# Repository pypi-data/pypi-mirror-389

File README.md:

# PyPI code 389

This repository is part of a project to make all code in PyPI as accessible as possible. For more information 
on the project and to find out how to utilise this data, see the website: https://py-code.org/

This repo contains 50000 packages uploaded to PyPI between 
2025-11-03 04:11 and 2025-11-06 15:08.

The repo is 99% (49999/50000) complete.

Package contents can be found [in the code branch](https://github.com/pypi-data/pypi-mirror-389/tree/code/packages).

A browsable package list for all repositories [all packages here](https://py-code.org/repositories/pypi-mirror-389).

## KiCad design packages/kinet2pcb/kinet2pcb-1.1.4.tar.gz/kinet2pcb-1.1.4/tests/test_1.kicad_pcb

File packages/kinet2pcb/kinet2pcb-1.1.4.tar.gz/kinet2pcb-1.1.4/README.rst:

=========
kinet2pcb
=========

.. image:: https://img.shields.io/pypi/v/kinet2pcb.svg
        :target: https://pypi.python.org/pypi/kinet2pcb

Convert KiCad netlist into a PCBNEW ``.kicad_pcb`` file.

* Free software: MIT license
* Documentation: https://devbisme.github.io/kinet2pcb .

Features
--------

* Converts a KiCad netlist file into a ``.kicad_pcb`` file that can be edited with PCBNEW.

Credits
-------

This package was created with Cookiecutter_ and the `audreyr/cookiecutter-pypackage`_ project template.

.. _Cookiecutter: https://github.com/audreyr/cookiecutter
.. _`audreyr/cookiecutter-pypackage`: https://github.com/audreyr/cookiecutter-pypackage

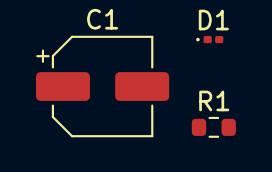
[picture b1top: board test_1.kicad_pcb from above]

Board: 2 copper layers, 3 parts (0 on the bottom side), 3 nets, no tracks yet.

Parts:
C1: C; CP_Elec_5x3
D1: LED; LED_0201_0603Metric
R1: R; R_0603_1608Metric

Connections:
unnamed: C1.1, D1.1
unnamed: C1.2, R1.2
unnamed: D1.2, R1.1

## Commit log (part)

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2025-11-07 Add package cisco-radkit-common/1.9.0/cisco_radkit_common-1.9.0-cp313-none-win_amd64.whl
2025-11-07 Add package dragon-ml-toolbox/15.1.0/dragon_ml_toolbox-15.1.0-py3-none-any.whl
2025-11-07 Add package gaftools/1.3.0/gaftools-1.3.0.tar.gz
2025-11-07 Add package eodash_catalog/0.3.18/eodash_catalog-0.3.18.tar.gz
2025-11-07 Add package pygeofilter-aeronet/0.2.0/pygeofilter_aeronet-0.2.0.tar.gz
2025-11-07 Add package abxrcli/0.14.0/abxrcli-0.14.0-py3-none-any.whl
2025-11-07 Add package tostorchconnector/1.1.1/tostorchconnector-1.1.1-py3-none-any.whl
2025-11-07 Add package aitrados-ctp/0.0.1/aitrados_ctp-0.0.1.tar.gz
2025-11-07 Add package shellfit/26.10.2025/shellfit-26.10.2025-py3-none-any.whl
2025-11-07 Add package pygeofilter-aeronet/0.2.0/pygeofilter_aeronet-0.2.0-py3-none-any.whl
2025-11-07 Add package scc-firewall-manager-sdk/1.15.386/scc_firewall_manager_sdk-1.15.386-py3-none-any.whl
2025-11-07 Add package agentlys-tools/0.2.0/agentlys_tools-0.2.0.tar.gz
2025-11-07 Add package shellfit/26.10.2025/shellfit-26.10.2025.tar.gz
2025-11-07 Add package webbed-duck/0.32.1/webbed_duck-0.32.1-py3-none-any.whl
2025-11-07 Add package zetsubou-sdk/1.0.0/zetsubou_sdk-1.0.0-py3-none-any.whl
2025-11-07 Add package webbed-duck/0.32.1/webbed_duck-0.32.1.tar.gz
2025-11-07 Add package apify-client/2.2.2b4/apify_client-2.2.2b4-py3-none-any.whl
2025-11-07 Add package llama-deploy-appserver/0.3.20/llama_deploy_appserver-0.3.20-py3-none-any.whl
2025-11-07 Add package any-llm-sdk/1.2.0/any_llm_sdk-1.2.0-py3-none-any.whl
2025-11-07 Add package lumen-python-sdk/0.1.1/lumen_python_sdk-0.1.1.tar.gz
2025-11-07 Add package llamactl/0.3.20/llamactl-0.3.20-py3-none-any.whl
2025-11-07 Add package llama-deploy-core/0.3.20/llama_deploy_core-0.3.20.tar.gz
2025-11-07 Add package lumen-python-sdk/0.1.1/lumen_python_sdk-0.1.1-py3-none-any.whl
2025-11-07 Add package chellow/1762435291.0.0/chellow-1762435291.0.0-py3-none-any.whl
2025-11-07 Add package glycorender/0.2.3/glycorender-0.2.3.tar.gz
2025-11-07 Add package intentkit/0.8.22.dev5/intentkit-0.8.22.dev5.tar.gz
2025-11-07 Add package axmp-openapi-helper/0.2.0/axmp_openapi_helper-0.2.0.tar.gz
2025-11-07 Add package xaiographs/2.0.0/xaiographs-2.0.0-py3-none-any.whl
2025-11-07 Add package egasp/0.1.4/egasp-0.1.4-py3-none-any.whl
2025-11-07 Add package seqcalc/0.0.2/seqcalc-0.0.2-py3-none-any.whl
2025-11-07 Add package coiled/1.129.1.dev9/coiled-1.129.1.dev9-py3-none-any.whl
2025-11-07 Add package mphot/1.2.3/mphot-1.2.3-py3-none-any.whl
2025-11-07 Add package epics-sumo/4.7.1/epics_sumo-4.7.1-py3-none-any.whl
2025-11-07 Add package changepacks/0.1.23/changepacks-0.1.23-py3-none-manylinux_2_17_armv7l.manylinux2014_armv7l.whl
2025-11-07 Add package invenio-app-ils/6.1.0/invenio_app_ils-6.1.0.tar.gz
2025-11-07 Add package ai-selector/0.1.1/ai_selector-0.1.1.tar.gz
2025-11-07 Add package seqcalc/0.0.2/seqcalc-0.0.2.tar.gz
2025-11-07 Add package mkf/0.1.0/mkf-0.1.0.tar.gz
2025-11-07 Add package coiled/1.129.1.dev9/coiled-1.129.1.dev9.tar.gz
2025-11-07 Add package pulumi-akamai/10.1.0/pulumi_akamai-10.1.0-py3-none-any.whl
2025-11-07 Add package ai-selector/0.1.1/ai_selector-0.1.1-py3-none-any.whl
2025-11-07 Add package changepacks/0.1.23/changepacks-0.1.23-py3-none-manylinux_2_17_aarch64.manylinux2014_aarch64.whl
2025-11-07 Add package chuk-mcp-runtime/0.9.0/chuk_mcp_runtime-0.9.0-py3-none-any.whl
2025-11-07 Add package tensordict-nightly/2025.11.6/tensordict_nightly-2025.11.6-cp311-cp311-macosx_15_0_universal2.whl
2025-11-07 Add package tensordict-nightly/2025.11.6/tensordict_nightly-2025.11.6-cp314-cp314-macosx_15_0_universal2.whl
2025-11-07 Add package tensordict-nightly/2025.11.6/tensordict_nightly-2025.11.6-cp312-cp312-macosx_15_0_universal2.whl
2025-11-07 Add package mphot/1.2.3/mphot-1.2.3.tar.gz
2025-11-07 Add package my-cli-utilities/0.3.8/my_cli_utilities-0.3.8.tar.gz
2025-11-07 Add package changepacks/0.1.23/changepacks-0.1.23-py3-none-manylinux_2_17_x86_64.manylinux2014_x86_64.whl
2025-11-07 Add package malifiscan/0.13/malifiscan-0.13-py3-none-any.whl
2025-11-07 Add package wds-client/0.38.33/wds_client-0.38.33.tar.gz
2025-11-07 Add package codemie-tools/0.1.11.4/codemie_tools-0.1.11.4.tar.gz
2025-11-07 Add package tensordict-nightly/2025.11.6/tensordict_nightly-2025.11.6-cp312-cp312-manylinux1_x86_64.whl
2025-11-07 Add package catrxneng/1.0.34/catrxneng-1.0.34-py3-none-any.whl
2025-11-07 Add package the37lab-authlib/0.1.1762440697/the37lab_authlib-0.1.1762440697.tar.gz
2025-11-07 Add package fastapi-blocks-registry/0.2.12/fastapi_blocks_registry-0.2.12-py3-none-any.whl
2025-11-07 Add package x-transformers/2.11.17/x_transformers-2.11.17.tar.gz
2025-11-07 Add package panda-client-light/1.6.3/panda_client_light-1.6.3-py2.py3-none-any.whl
2025-11-07 Add package AOT-biomaps/2.9.233/aot_biomaps-2.9.233.tar.gz
2025-11-07 Add package xstatix/1.2.0/xstatix-1.2.0.tar.gz
2025-11-07 Add package ase-ga/1.0.3/ase_ga-1.0.3.tar.gz
2025-11-07 Add package AOT-biomaps/2.9.233/aot_biomaps-2.9.233-py3-none-any.whl
2025-11-07 Add package tensordict-nightly/2025.11.6/tensordict_nightly-2025.11.6-cp314-cp314-manylinux1_x86_64.whl
2025-11-07 Add package ase-ga/1.0.3/ase_ga-1.0.3-py3-none-any.whl
2025-11-07 Add package tensordict-nightly/2025.11.6/tensordict_nightly-2025.11.6-cp311-cp311-manylinux1_x86_64.whl
2025-11-07 Add package changepacks/0.1.23/changepacks-0.1.23-py3-none-macosx_10_12_x86_64.whl
2025-11-07 Add package changepacks/0.1.23/changepacks-0.1.23-py3-none-musllinux_1_2_x86_64.whl
2025-11-07 Add package langchain-azure-ai/1.0.3/langchain_azure_ai-1.0.3-py3-none-any.whl
2025-11-07 Add package changepacks/0.1.23/changepacks-0.1.23-py3-none-win_amd64.whl
2025-11-07 Add package ai21/4.3.0/ai21-4.3.0-py3-none-any.whl
2025-11-07 Add package odoo-addon-delivery-dhl-parcel/18.0.1.0.0.3/odoo_addon_delivery_dhl_parcel-18.0.1.0.0.3-py3-none-any.whl
2025-11-07 Add package rgmol/0.1.4.4/rgmol-0.1.4.4.tar.gz
2025-11-07 Add package stacking-2d-systems/0.1.2/stacking_2d_systems-0.1.2.tar.gz
2025-11-07 Add package mcasm/0.4.0/mcasm-0.4.0-cp38-cp38-manylinux_2_12_x86_64.manylinux2010_x86_64.whl
2025-11-07 Add package zjt-sun/0.1.0/zjt_sun-0.1.0-py3-none-any.whl
2025-11-07 Add package mcasm/0.4.0/mcasm-0.4.0-cp37-cp37m-manylinux_2_12_x86_64.manylinux2010_x86_64.whl
2025-11-07 Add package ai21/4.3.0/ai21-4.3.0.tar.gz
2025-11-07 Add package seraa/0.2.1/seraa-0.2.1-py3-none-any.whl
2025-11-07 Add package zulmorph/1.0.1/zulmorph-1.0.1.tar.gz
2025-11-07 Add package git-llm-tool/0.1.5/git_llm_tool-0.1.5.tar.gz
2025-11-07 Add package pygram11/0.15.0/pygram11-0.15.0-cp311-cp311-manylinux_2_24_aarch64.manylinux_2_28_aarch64.whl
2025-11-07 Add package power-grid-model/1.12.64/power_grid_model-1.12.64-py3-none-macosx_13_0_arm64.whl
2025-11-07 Add package power-grid-model/1.12.64/power_grid_model-1.12.64-py3-none-manylinux_2_24_aarch64.manylinux_2_28_aarch64.whl
2025-11-07 Add package nkutils/0.1.2/nkutils-0.1.2.tar.gz
2025-11-07 Add package mcasm/0.4.0/mcasm-0.4.0-cp38-cp38-win_amd64.whl
2025-11-07 Add package pygram11/0.15.0/pygram11-0.15.0-cp311-cp311-manylinux2014_x86_64.manylinux_2_17_x86_64.whl
2025-11-07 Add package scc-firewall-manager-sdk/1.15.387/scc_firewall_manager_sdk-1.15.387-py3-none-any.whl
2025-11-07 Add package opentelemetry-instrumentation-kstreams/0.5.1rc0.dev191400071044/opentelemetry_instrumentation_kstreams-0.5.1rc0.dev191400071044-py3-none-any.whl
2025-11-07 Add package pygram11/0.15.0/pygram11-0.15.0-cp311-cp311-win32.whl
2025-11-07 Add package power-grid-model/1.12.64/power_grid_model-1.12.64-py3-none-win_amd64.whl
2025-11-07 Add package power-grid-model/1.12.64/power_grid_model-1.12.64-py3-none-musllinux_1_2_x86_64.whl
2025-11-07 Add package mikro-next/0.19.0/mikro_next-0.19.0-py3-none-any.whl
2025-11-07 Add package pygram11/0.15.0/pygram11-0.15.0-cp312-cp312-manylinux_2_24_aarch64.manylinux_2_28_aarch64.whl
2025-11-07 Add package rtorrent-rpc/0.9.5a0/rtorrent_rpc-0.9.5a0-py3-none-any.whl
2025-11-07 Add package pygram11/0.15.0/pygram11-0.15.0-cp313-cp313-win32.whl
2025-11-07 Add package power-grid-model/1.12.64/power_grid_model-1.12.64.tar.gz
2025-11-07 Add package pygram11/0.15.0/pygram11-0.15.0-cp312-cp312-macosx_14_0_arm64.whl
2025-11-07 Add package pygeofilter-aeronet/0.1.0/pygeofilter_aeronet-0.1.0.tar.gz
2025-11-07 Add package windmill-api/1.573.3/windmill_api-1.573.3.tar.gz
2025-11-07 Add package biochatter/0.14.0/biochatter-0.14.0-py3-none-any.whl
2025-11-07 Add package pygram11/0.15.0/pygram11-0.15.0-cp313-cp313-manylinux_2_24_aarch64.manylinux_2_28_aarch64.whl
2025-11-07 Add package pygram11/0.15.0/pygram11-0.15.0-cp313-cp313-macosx_14_0_arm64.whl
2025-11-07 Add package pygram11/0.15.0/pygram11-0.15.0-cp313-cp313-musllinux_1_2_x86_64.whl
2025-11-07 Add package mxm-scaffold/0.18.5.dev62339673/mxm_scaffold-0.18.5.dev62339673-py3-none-any.whl
2025-11-07 Add package unimpeded/0.2.7/unimpeded-0.2.7-py3-none-any.whl
2025-11-07 Add package pygram11/0.15.0/pygram11-0.15.0-cp312-cp312-win_amd64.whl
2025-11-07 Add package pygram11/0.15.0/pygram11-0.15.0-cp314-cp314-musllinux_1_2_aarch64.whl
2025-11-07 Add package pygram11/0.15.0/pygram11-0.15.0-cp313-cp313-win_amd64.whl
2025-11-07 Add package peoplequant/1.0.1/peoplequant-1.0.1-py3-none-any.whl
2025-11-07 Add package AgentToolProtocol/0.2.2/agenttoolprotocol-0.2.2.tar.gz
2025-11-07 Add package pygram11/0.15.0/pygram11-0.15.0-cp314-cp314t-manylinux2014_x86_64.manylinux_2_17_x86_64.whl
2025-11-07 Add package nsj-multi-database-lib/2.0.2/nsj_multi_database_lib-2.0.2-py3-none-any.whl
2025-11-07 Add package artistools/2025.11.6/artistools-2025.11.6-cp313-cp313-manylinux_2_28_aarch64.whl
2025-11-07 Add package artistools/2025.11.6/artistools-2025.11.6-cp313-cp313-macosx_13_0_arm64.whl
2025-11-07 Add package shikou-lib/0.0.1/shikou_lib-0.0.1.tar.gz
2025-11-07 Add package shikou-lib/0.0.1/shikou_lib-0.0.1-py3-none-any.whl
2025-11-07 Add package nsj-multi-database-lib/2.0.2/nsj_multi_database_lib-2.0.2.tar.gz
2025-11-07 Add package gs-batch-pdf/0.6.1/gs_batch_pdf-0.6.1-py3-none-any.whl
2025-11-07 Add package pygram11/0.15.0/pygram11-0.15.0-cp314-cp314t-musllinux_1_2_x86_64.whl
2025-11-07 Add package cv-toolkit-takaw/0.1.0/cv_toolkit_takaw-0.1.0-py3-none-any.whl
2025-11-07 Add package respick/0.1.6/respick-0.1.6.tar.gz
2025-11-07 Add package sirabus/0.7.0/sirabus-0.7.0-py3-none-any.whl
2025-11-07 Add package bimdata-api-client/10.23.3/bimdata_api_client-10.23.3.tar.gz
2025-11-07 Add package artistools/2025.11.6/artistools-2025.11.6-cp314-cp314-manylinux_2_28_aarch64.whl
2025-11-07 Add package zetsubou-sdk/1.0.1/zetsubou_sdk-1.0.1.tar.gz
2025-11-07 Add package rimopy/0.3.0/rimopy-0.3.0-py3-none-any.whl
2025-11-07 Add package ms2deepscore/2.5.5/ms2deepscore-2.5.5.tar.gz
2025-11-07 Add package zetsubou-sdk/1.0.1/zetsubou_sdk-1.0.1-py3-none-any.whl
2025-11-07 Add package axmp-openapi-mcp-server/0.2.1/axmp_openapi_mcp_server-0.2.1.tar.gz
2025-11-07 Add package agentscope-runtime/0.2.0/agentscope_runtime-0.2.0-py3-none-any.whl
2025-11-07 Add package axmp-openapi-mcp-server/0.2.1/axmp_openapi_mcp_server-0.2.1-py3-none-any.whl
2025-11-07 Add package macrotools/0.1.0/macrotools-0.1.0.tar.gz
2025-11-07 Add package qoqo-qasm/0.15.3/qoqo_qasm-0.15.3-cp311-cp311-macosx_10_12_x86_64.macosx_11_0_arm64.macosx_10_12_universal2.whl
2025-11-07 Add package qoqo-qasm/0.15.3/qoqo_qasm-0.15.3-cp312-cp312-macosx_10_12_x86_64.macosx_11_0_arm64.macosx_10_12_universal2.whl
2025-11-07 Add package artistools/2025.11.6/artistools-2025.11.6-cp311-cp311-manylinux_2_28_x86_64.whl
2025-11-07 Add package maptasker/9.0.5/maptasker-9.0.5-py3-none-any.whl
2025-11-07 Add package artistools/2025.11.6/artistools-2025.11.6.tar.gz
2025-11-07 Add package veridica/0.1.0/veridica-0.1.0-py3-none-any.whl
2025-11-07 Add package pargs-sfe/0.1.1/pargs_sfe-0.1.1-py3-none-any.whl
2025-11-07 Add package qoqo-qasm/0.15.3/qoqo_qasm-0.15.3-cp312-cp312-manylinux_2_17_x86_64.manylinux2014_x86_64.whl
2025-11-07 Add package genailib/0.1.4/genailib-0.1.4.tar.gz
2025-11-07 Add package qoqo-qasm/0.15.3/qoqo_qasm-0.15.3.tar.gz
2025-11-07 Add package semgrep/1.142.1/semgrep-1.142.1-cp310.cp311.cp312.cp313.cp314.py310.py311.py312.py313.py314-none-macosx_10_14_x86_64.whl
